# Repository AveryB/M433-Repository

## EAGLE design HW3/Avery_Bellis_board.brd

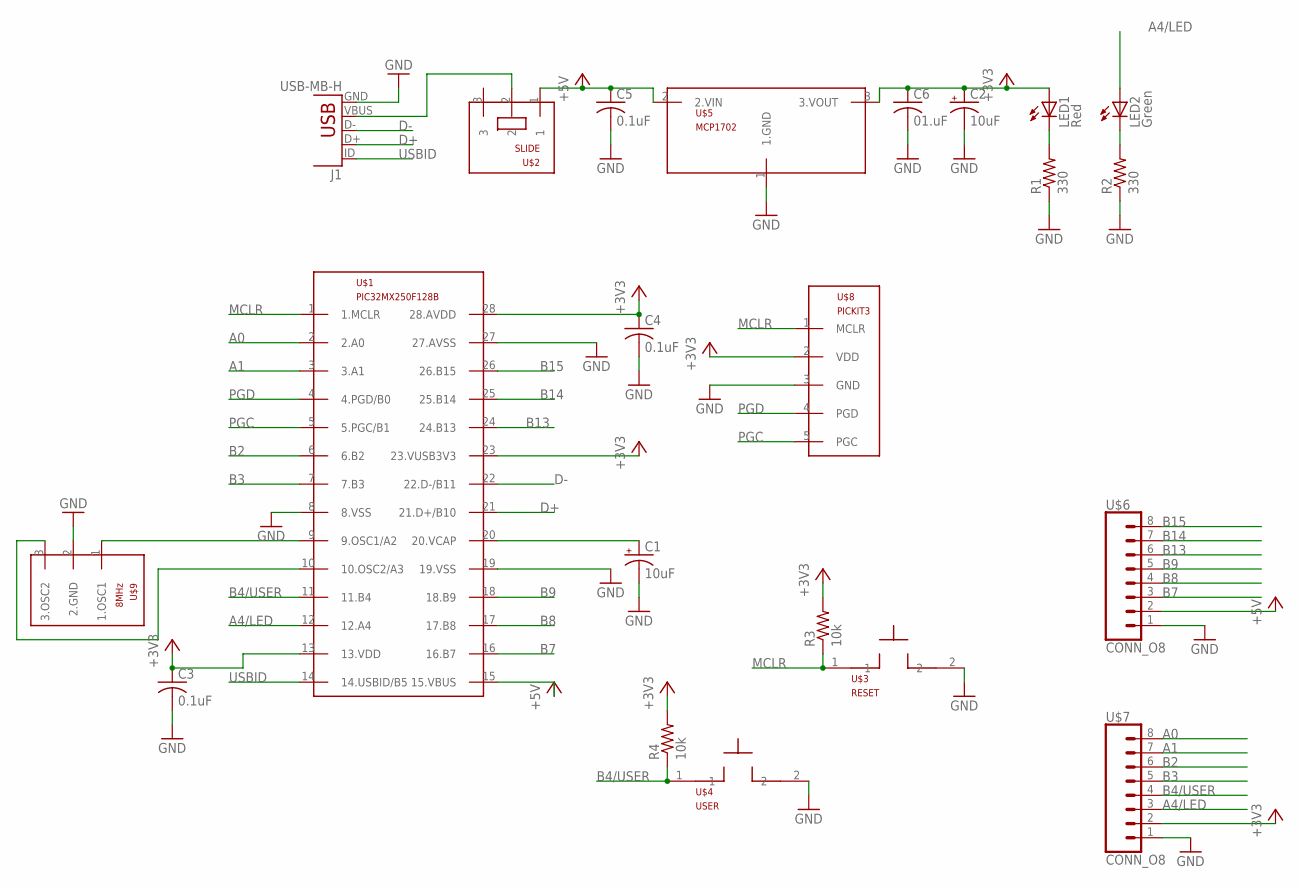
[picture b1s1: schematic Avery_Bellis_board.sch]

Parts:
C1, C2: 10uF; B45181B
C3, C4, C5: 0.1uF; C025-025X050
C6: 01.uF; C025-025X050
J1: USB-MB-H
LED1: Red; LED3MM
LED2: Green; LED3MM
R1, R2: 330; 0207/10
R3, R4: 10k; 0207/10
U$1: PIC32MX250F128B; DIL28-3
U$2: SLIDE
U$3: RESET; PUSHB
U$4: USER; PUSHB
U$5: MCP1702; TO92
U$6, U$7: CONN_O8; 1X08
U$8: PICKIT3; 1X05
U$9: 8MHz; OSC

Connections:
+3V3: C2.+, C3.1, C4.1, C6.1, LED1.A, R3.2, R4.2, U$1.13 (13.VDD), U$1.23 (23.VUSB3V3), U$1.28 (28.AVDD), U$5.3 (3.VOUT), U$7.2, U$8.2 (VDD)
+5V: C5.1, U$1.15 (15.VBUS), U$2.1, U$5.2 (2.VIN), U$6.2
A0: U$1.2 (2.A0), U$7.8
A1: U$1.3 (3.A1), U$7.7
A4/LED: LED2.A, U$1.12 (12.A4), U$7.3
B2: U$1.6 (6.B2), U$7.6
B3: U$1.7 (7.B3), U$7.5
B4/USER: R4.1, U$1.11 (11.B4), U$4.1, U$7.4
B7: U$1.16 (16.B7), U$6.3
B8: U$1.17 (17.B8), U$6.4
B9: U$1.18 (18.B9), U$6.5
B13: U$1.24 (24.B13), U$6.6
B14: U$1.25 (25.B14), U$6.7
B15: U$1.26 (26.B15), U$6.8
D+: J1.D+, U$1.21 (21.D+/B10)
D-: J1.D-, U$1.22 (22.D-/B11)
GND: C1.-, C2.-, C3.2, C4.2, C5.2, C6.2, J1.GND, R1.1, R2.1, U$1.8 (8.VSS), U$1.19 (19.VSS), U$1.27 (27.AVSS), U$3.2, U$4.2, U$5.1 (1.GND), U$6.1, U$7.1, U$8.3 (GND), U$9.2 (2.GND)
MCLR: R3.1, U$1.1 (1.MCLR), U$3.1, U$8.1 (MCLR)
unnamed: J1.VBUS, U$2.2
unnamed: LED2.K (C), R2.2
unnamed: LED1.K (C), R1.2
unnamed: U$1.9 (9.OSC1/A2), U$9.1 (1.OSC1)
unnamed: U$1.10 (10.OSC2/A3), U$9.3 (3.OSC2)
unnamed: C1.+, U$1.20 (20.VCAP)
PGC: U$1.5 (5.PGC/B1), U$8.5 (PGC)
PGD: U$1.4 (4.PGD/B0), U$8.4 (PGD)
USBID: J1.ID, U$1.14 (14.USBID/B5)

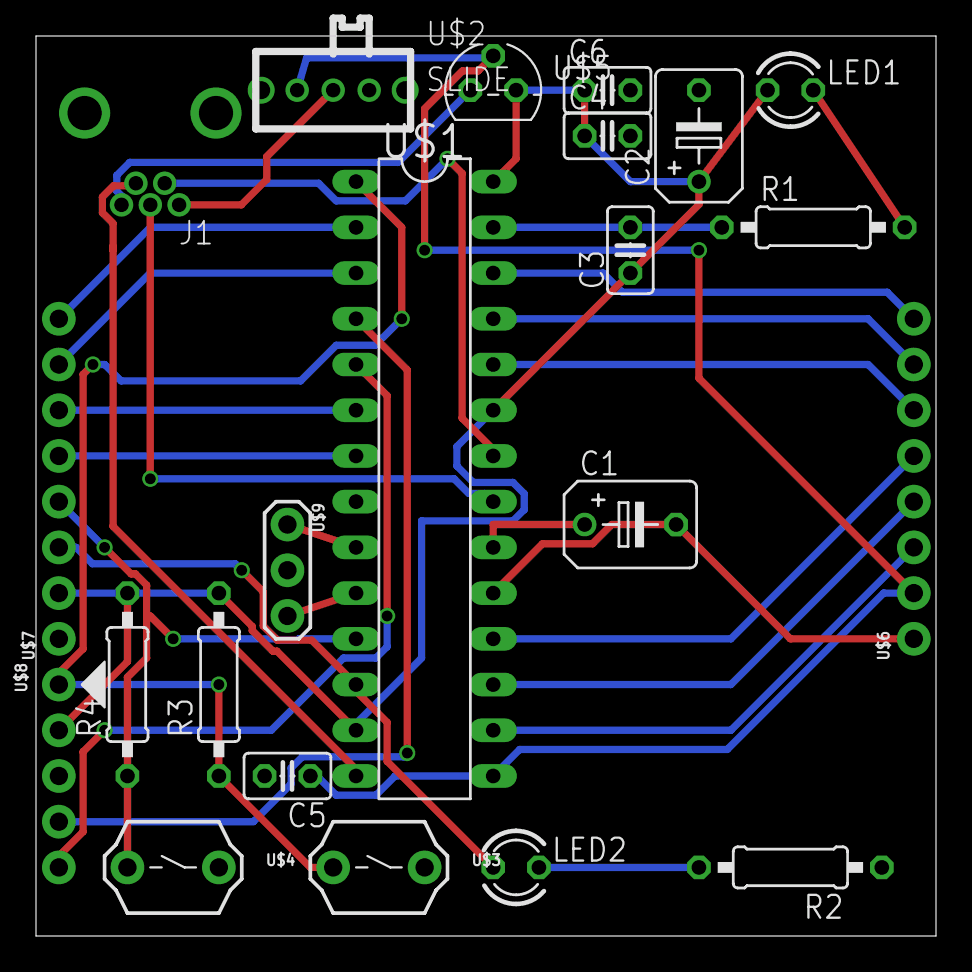
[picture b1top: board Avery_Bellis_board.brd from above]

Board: 2 copper layers, 50.0 x 50.0 mm, 22 parts (0 on the bottom side), 27 nets.

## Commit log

2017-03-31 :space_invader: Added .gitattributes & .gitignore files
2017-03-31 Uploaded Homework1
2017-04-03 Added Video and Circuit photo
2017-04-05 Uploading HW2 Library and Schematic
2017-04-11 Uploading Home Work 3
2017-04-14 Upload HW4
2017-04-17 Included correct C file for HW 1
2017-04-18 Uploaded HW4 Schematic
2017-04-18 Code updated
2017-04-21 Uploading final HW 4 code
2017-04-21 Uploading HW 4 Sine/Rampwave video
2017-04-21 HW5 Schematic
2017-04-24 Upload HW5 template
2017-04-24 Uploading HW6 Template
2017-04-24 HW6 Addition
2017-04-24 HW6_2
2017-04-24 HW_3&HW_4
2017-04-24 HW6_5
2017-05-05 Upload HW5_2
2017-05-12 Upload HW6
2017-05-15 HW6Update
2017-05-15 6_12
2017-05-15 Final HW6
2017-05-26 FinalHW5 Upload
2017-05-26 Uploading HW17
2017-05-26 Adding Video for HW5
2017-05-26 Uploading HW12 project and HW13 Project
2017-05-26 Upload HW13 Video
2017-05-26 Upload HW 12 Video
2017-05-30 Uploading HW15
2017-05-31 Uploading HW 16
2017-06-09 Upload HW 9
2017-06-09 Upload HW 18
2017-06-11 Upload HW 19 and HW 20
2017-06-11 Upload HW 20
